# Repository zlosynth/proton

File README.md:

# Proton

Playground module for eurorack prototyping.

* This is meant to help to test ideas of new modules before they get their own
  custom hardware.
* This is not meant to be stable or simple.

# Development

See [DEVELOPMENT.md](DEVELOPMENT.md) to find some basic commands to interact
with the project.

# License

Software of Proton is distributed under the terms of the General Public
License version 3. See [LICENSE-SOFTWARE](LICENSE-SOFTWARE) for details.

Schematics and PCB layout are distributed under the terms of Creative Commons
BY-SA. See [LICENSE-HARDWARE](LICENSE-HARDWARE) for details. Parts of the
schematics are based on [Emilie Gillet's Mutable
Instruments](https://github.com/pichenettes/eurorack) and [Electrosmith's
Patch](https://www.electro-smith.com/daisy/patch) kudos to them for making them
open.

# Changelog

Read the [CHANGELOG.md](CHANGELOG.md) to learn about changes introduced in each
release.

# Versioning

See [VERSIONING.md](VERSIONING.md) to find detailed information about versioning
of the project and compatability between its software and hardware.

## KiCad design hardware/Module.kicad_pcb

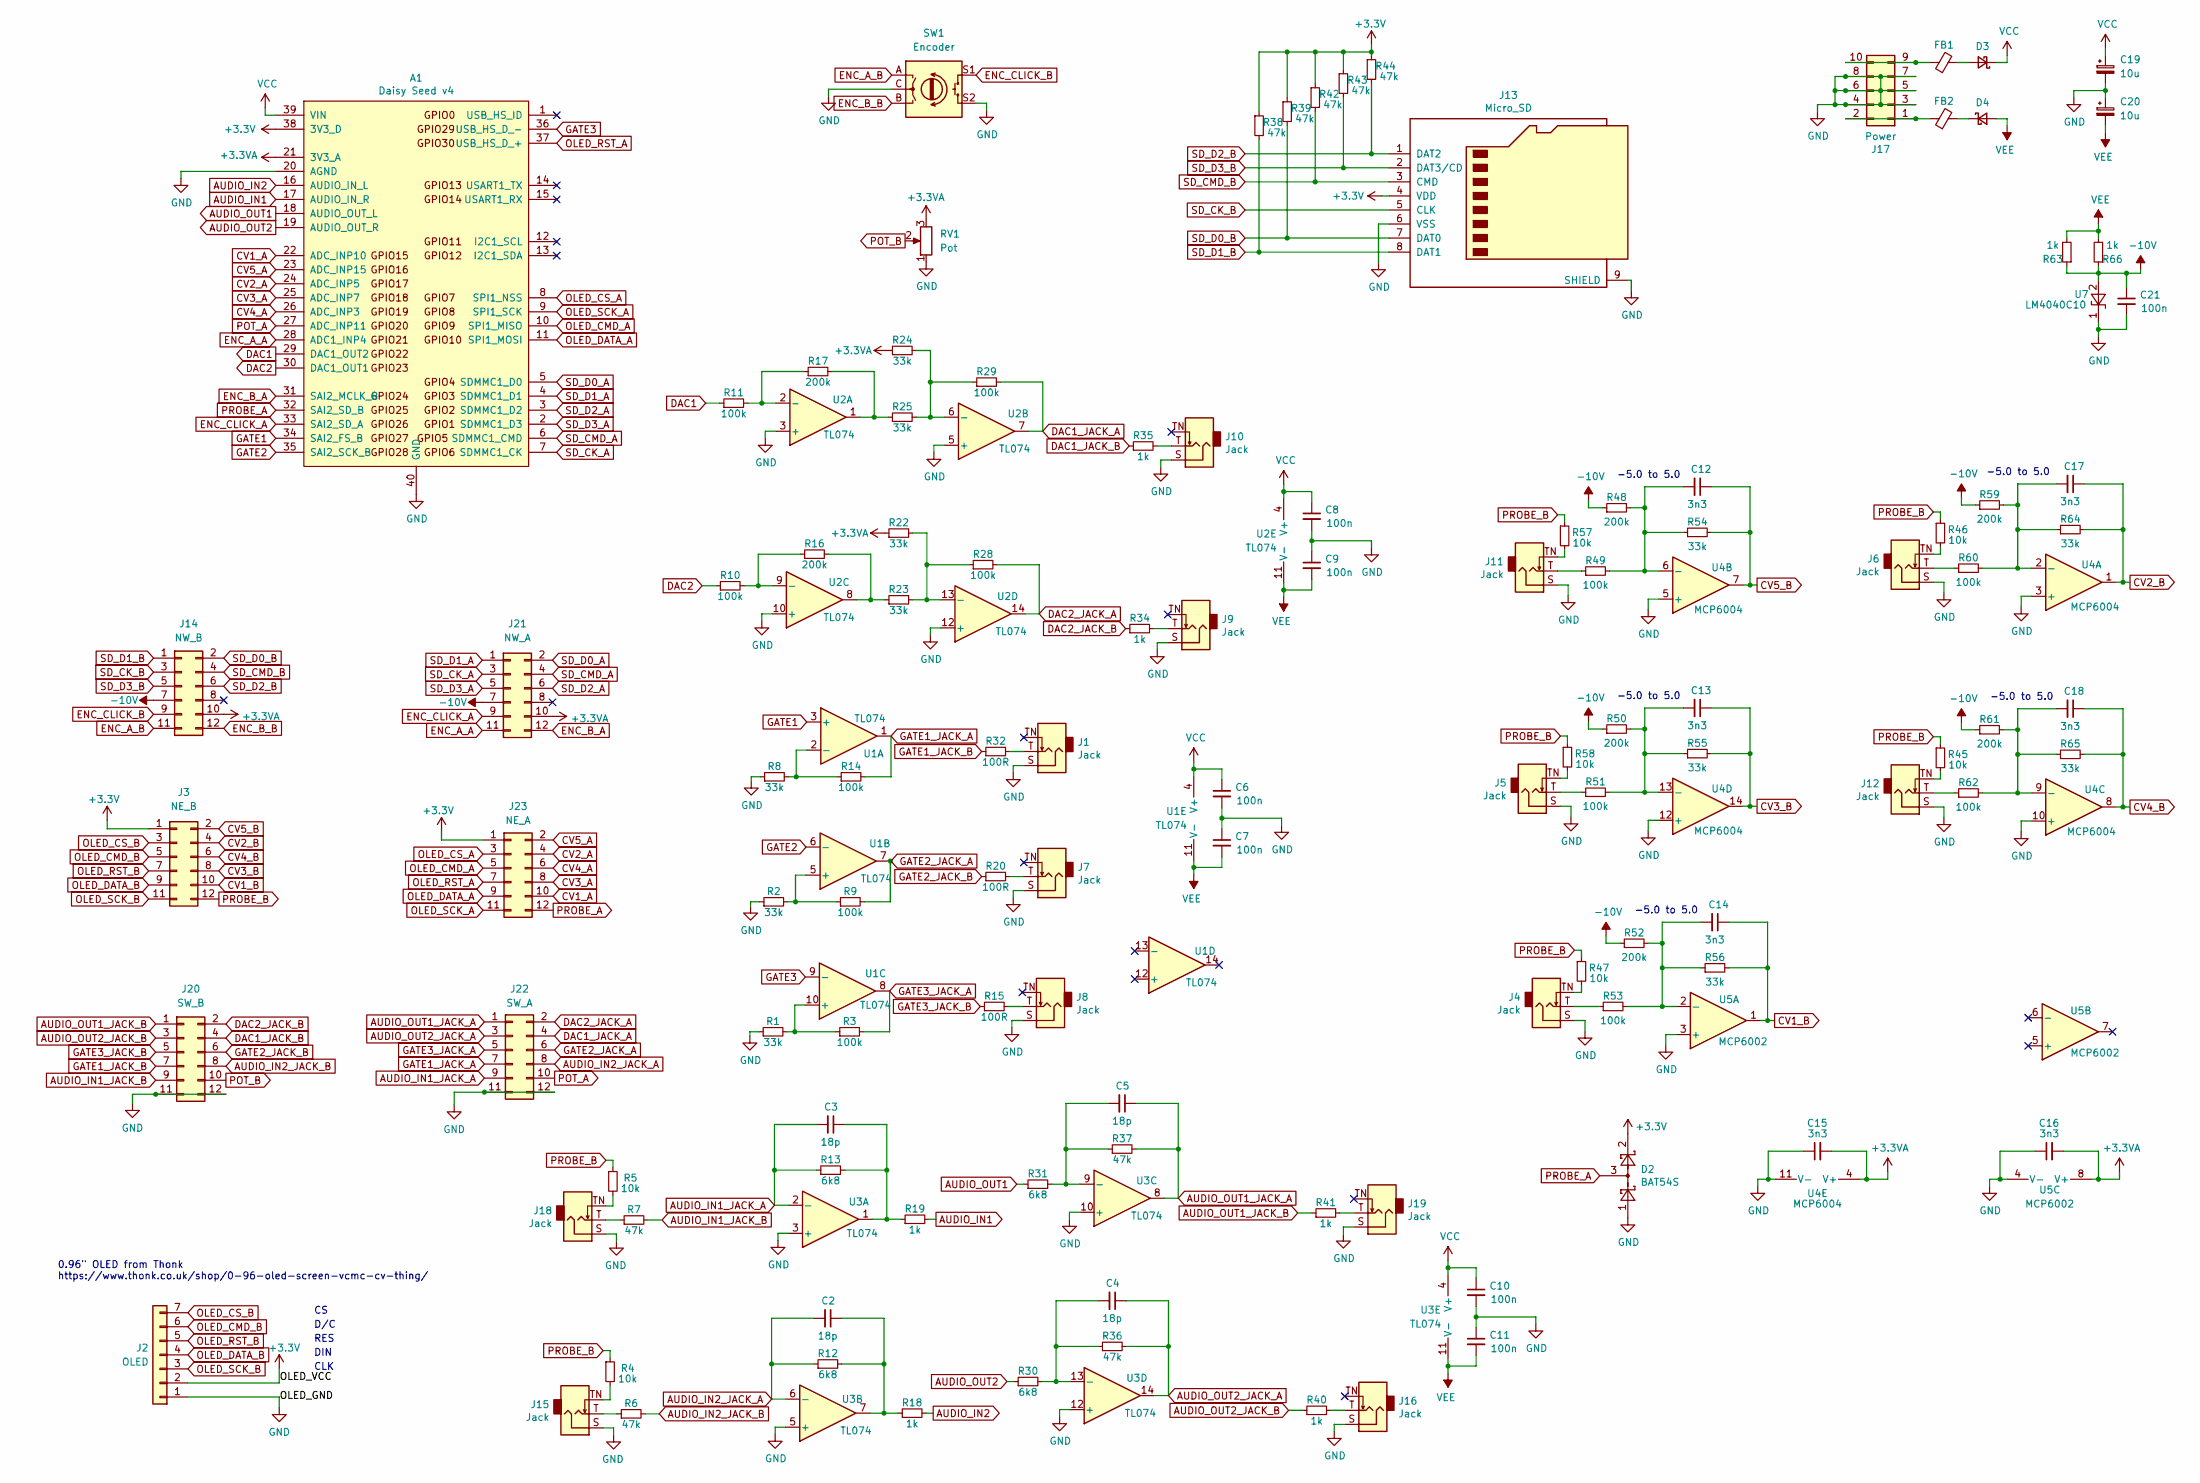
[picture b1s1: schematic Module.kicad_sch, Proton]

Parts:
A1: Daisy Seed v4; Device_Audio_Electrosmith_Daisy_Seed; Mfr Part Number M20-7822046
C2, C3, C4, C5: 18p; C_0603_1608Metric_Pad1.08x0.95mm_HandSolder; Mfr Part Number CL10C180JB81PNC; LCSC C1647
C6, C7, C8, C9, C10, C11: 100n; C_0603_1608Metric_Pad1.08x0.95mm_HandSolder; Mfr Part Number CL10F104ZO8NNNC; LCSC C14663
C12, C13, C14, C15, C16, C17, C18: 3n3; C_0603_1608Metric_Pad1.08x0.95mm_HandSolder; Mfr Part Number CL10B332KB8NNNC; LCSC C1613
C19, C20: 10u; CP_Elec_6.3x5.8
C21: 100n; C_0603_1608Metric_Pad1.08x0.95mm_HandSolder; Mfr Part Number CL31B104KBCNNNL; LCSC C24497
D2: BAT54S; SOT-23_Handsoldering; Mfr Part Number BAT54S,215
D3, D4: Schottky; D_SOD-123; Mfr Part Number STPS0540ZY; LCSC C8598
FB1, FB2: FB; L_0603_1608Metric_Pad1.05x0.95mm_HandSolder
J1, J4, J5, J6, J7, J8, J9, J10, J11, J12, J15, J16, J18, J19: Jack; Jack_3.5mm_QingPu_WQP-PJ398SM_Vertical_CircularHoles
J2: OLED; PinSocket_1x07_P2.54mm_Vertical
J3: NE_B; PinSocket_2x06_P2.54mm_Vertical
J13: Micro_SD; microsd_connector
J14: NW_B; PinSocket_2x06_P2.54mm_Vertical
J17: Power; PinHeader_2x05_P2.54mm_Vertical; Mfr Part Number 87914-1016
J20: SW_B; PinSocket_2x06_P2.54mm_Vertical
J21: NW_A; PinHeader_2x06_P2.54mm_Vertical
J22: SW_A; PinHeader_2x06_P2.54mm_Vertical
J23: NE_A; PinHeader_2x06_P2.54mm_Vertical
R1, R2, R8, R22, R23, R24, R25: 33k; R_0603_1608Metric_Pad0.98x0.95mm_HandSolder; Mfr Part Number CR0603-JW-682ELF; LCSC C23212
R3, R9, R14, R28, R29: 100k; R_0603_1608Metric_Pad0.98x0.95mm_HandSolder; Mfr Part Number CR0603-FX-4702ELF; LCSC C25819
R4, R5, R45, R46, R47, R57, R58: 10k; R_0603_1608Metric_Pad0.98x0.95mm_HandSolder; Mfr Part Number CR0603-FX-1002ELF; LCSC C25744
R6, R7: 47k; R_0603_1608Metric_Pad0.98x0.95mm_HandSolder; Mfr Part Number CR0603-JW-682ELF; LCSC C23212
R10, R11: 100k; R_0603_1608Metric_Pad0.98x0.95mm_HandSolder; Mfr Part Number CR0603-JW-682ELF; LCSC C23212
R12, R13: 6k8; R_0603_1608Metric_Pad0.98x0.95mm_HandSolder; Mfr Part Number CR0603-FX-4702ELF; LCSC C25819
R15, R20, R32: 100R; R_0603_1608Metric_Pad0.98x0.95mm_HandSolder; Mfr Part Number CR0603-FX-1001ELF; LCSC C21190
R16, R17: 200k; R_0603_1608Metric_Pad0.98x0.95mm_HandSolder; Mfr Part Number CR0603-FX-4702ELF; LCSC C25819
R18, R19, R34, R35, R40, R41, R63, R66: 1k; R_0603_1608Metric_Pad0.98x0.95mm_HandSolder; Mfr Part Number CR0603-FX-1001ELF; LCSC C21190
R30, R31: 6k8; R_0603_1608Metric_Pad0.98x0.95mm_HandSolder; Mfr Part Number CR0603-JW-682ELF; LCSC C23212
R36, R37: 47k; R_0603_1608Metric_Pad0.98x0.95mm_HandSolder; Mfr Part Number CR0603-FX-4702ELF; LCSC C25819
R38, R39, R42, R43, R44: 47k; R_0603_1608Metric_Pad0.98x0.95mm_HandSolder; Mfr Part Number CR0603-FX-1002ELF; LCSC C25744
R48: 200k; R_0603_1608Metric_Pad0.98x0.95mm_HandSolder; Mfr Part Number CR0603-FX-1803ELF; LCSC C25808
R49, R51, R53, R60, R62: 100k; R_0603_1608Metric_Pad0.98x0.95mm_HandSolder; Mfr Part Number CR0603-JW-104ELF; LCSC C25803
R50: 200k; R_0603_1608Metric_Pad0.98x0.95mm_HandSolder; Mfr Part Number CR0603-FX-1203ELF; LCSC C22827
R52, R61: 200k; R_0603_1608Metric_Pad0.98x0.95mm_HandSolder; Mfr Part Number CR0603-FX-1203ELF; LCSC C25808
R54: 33k; R_0603_1608Metric_Pad0.98x0.95mm_HandSolder; Mfr Part Number CR0603-FX-4702ELF; LCSC C4184
R55: 33k; R_0603_1608Metric_Pad0.98x0.95mm_HandSolder; Mfr Part Number CR0603-FX-2002ELF; LCSC C25819
R56, R65: 33k; R_0603_1608Metric_Pad0.98x0.95mm_HandSolder; Mfr Part Number CR0603-FX-2002ELF; LCSC C4184
R59: 200k; R_0603_1608Metric_Pad0.98x0.95mm_HandSolder; Mfr Part Number CR0603-FX-1803ELF; LCSC C22827
R64: 33k; R_0603_1608Metric_Pad0.98x0.95mm_HandSolder; Mfr Part Number CR0603-FX-4702ELF; LCSC C25819
RV1: Pot; Potentiometer_Alpha_RD901F-40-00D_Single_Vertical
SW1: Encoder; RotaryEncoder_Alps_EC11E-Switch_Vertical_H20mm
U1, U2, U3: TL074; SOIC-14_3.9x8.7mm_P1.27mm
U4: MCP6004; SOIC-14_3.9x8.7mm_P1.27mm
U5: MCP6002; SOIC-8_3.9x4.9mm_P1.27mm; Mfr Part Number MCP6002-I/SN; LCSC C7377
U7: LM4040C10; SOT-23_Handsoldering; Mfr Part Number LM4040C10IDBZR; LCSC C201738

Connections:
+3.3VA: A1.21 (3V3_A), C15.2, C16.2, J14.10, J21.10, R22.1, R24.1, RV1.3, U4.4 (V+), U5.8 (V+)
+3V3: A1.38 (3V3_D), D2.2, J2.2, J3.1, J13.4 (VDD), J23.1, R38.1, R39.1, R42.1, R43.1, R44.1
-10V: C21.1, J14.7, J21.7, R48.1, R50.1, R52.1, R59.1, R61.1, R63.1, R66.1, U7.2 (A)
AUDIO_IN1: A1.17 (AUDIO_IN_R), R19.2
AUDIO_IN1_JACK_A: C3.2, J22.9, R13.1, U3.2 (-)
AUDIO_IN1_JACK_B: J20.9, R7.2
AUDIO_IN2: A1.16 (AUDIO_IN_L), R18.2
AUDIO_IN2_JACK_A: C2.2, J22.8, R12.1, U3.6 (-)
AUDIO_IN2_JACK_B: J20.8, R6.2
AUDIO_OUT1: A1.18 (AUDIO_OUT_L), R31.1
AUDIO_OUT1_JACK_A: C5.1, J22.1, R37.2, U3.8
AUDIO_OUT1_JACK_B: J20.1, R41.1
AUDIO_OUT2: A1.19 (AUDIO_OUT_R), R30.1
AUDIO_OUT2_JACK_A: C4.1, J22.3, R36.2, U3.14
AUDIO_OUT2_JACK_B: J20.3, R40.1
CV1_A: A1.22 (ADC_INP10), J23.10
CV1_B: C14.1, J3.10, R56.2, U5.1
CV2_A: A1.24 (ADC_INP5), J23.4
CV2_B: C17.1, J3.4, R64.2, U4.1
CV3_A: A1.25 (ADC_INP7), J23.8
CV3_B: C13.1, J3.8, R55.2, U4.14
CV4_A: A1.26 (ADC_INP3), J23.6
CV4_B: C18.1, J3.6, R65.2, U4.8
CV5_A: A1.23 (ADC_INP15), J23.2
CV5_B: C12.1, J3.2, R54.2, U4.7
DAC1: A1.29 (DAC1_OUT2), R11.1
DAC1_JACK_A: J22.4, R29.2, U2.7
DAC1_JACK_B: J20.4, R35.1
DAC2: A1.30 (DAC1_OUT1), R10.1
DAC2_JACK_A: J22.2, R28.2, U2.14
DAC2_JACK_B: J20.2, R34.1
ENC_A_A: A1.28 (ADC1_INP4), J21.11
ENC_A_B: J14.11, SW1.A
ENC_B_A: A1.31 (SAI2_MCLK_B), J21.12
ENC_B_B: J14.12, SW1.B
ENC_CLICK_A: A1.33 (SAI2_SD_A), J21.9
ENC_CLICK_B: J14.9, SW1.S1
GATE1: A1.34 (SAI2_FS_B), U1.3 (+)
GATE1_JACK_A: J22.7, R14.2, U1.1
GATE1_JACK_B: J20.7, R32.1
GATE2: A1.35 (SAI2_SCK_B), U1.6 (-)
GATE2_JACK_A: J22.6, R9.2, U1.7
GATE2_JACK_B: J20.6, R20.1
GATE3: A1.36 (USB_HS_D_-), U1.9 (-)
GATE3_JACK_A: J22.5, R3.2, U1.8
GATE3_JACK_B: J20.5, R15.1
GND: A1.20 (AGND), A1.40 (GND), C6.2, C7.1, C8.2, C9.1, C10.2, C11.1, C15.1, C16.1, C19.2, C20.1, C21.2, D2.1, J1.S, J2.1, J4.S, J5.S, J6.S, J7.S, J8.S, J9.S, J10.S, J11.S, J12.S, J13.6 (VSS), J13.9 (SHIELD), J15.S, J16.S, J17.3, J17.4, J17.5, J17.6, J17.7, J17.8, J18.S, J19.S, J20.11, J20.12, J22.11, J22.12, R1.1, R2.1, R8.1, RV1.1, SW1.C, SW1.S2, U2.3 (+), U2.5 (+), U2.10 (+), U2.12 (+), U3.3 (+), U3.5 (+), U3.10 (+), U3.12 (+), U4.3 (+), U4.5 (+), U4.10 (+), U4.11 (V-), U4.12 (+), U5.3 (+), U5.4 (V-), U7.1 (K)
unnamed: C2.1, R12.2, R18.1, U3.7
unnamed: C3.1, R13.2, R19.1, U3.1
unnamed: C4.2, R30.2, R36.1, U3.13 (-)
unnamed: C5.2, R31.2, R37.1, U3.9 (-)
unnamed: C12.2, R48.2, R49.2, R54.1, U4.6 (-)
unnamed: C13.2, R50.2, R51.2, R55.1, U4.13 (-)
unnamed: C14.2, R52.2, R53.2, R56.1, U5.2 (-)
unnamed: C17.2, R59.2, R60.2, R64.1, U4.2 (-)
unnamed: C18.2, R61.2, R62.2, R65.1, U4.9 (-)
unnamed: D3.2 (A), FB1.2
unnamed: D4.1 (K), FB2.2
unnamed: FB1.1, J17.9, J17.10
unnamed: FB2.1, J17.1, J17.2
unnamed: J1.T, R32.2
unnamed: J4.T, R53.1
unnamed: J4.TN, R47.2
unnamed: J5.T, R51.1
unnamed: J5.TN, R58.2
unnamed: J6.T, R60.1
unnamed: J6.TN, R46.2
unnamed: J7.T, R20.2
unnamed: J8.T, R15.2
unnamed: J9.T, R34.2
unnamed: J10.T, R35.2
unnamed: J11.T, R49.1
unnamed: J11.TN, R57.2
unnamed: J12.T, R62.1
unnamed: J12.TN, R45.2
unnamed: J15.T, R6.1
unnamed: J15.TN, R4.2
unnamed: J16.T, R40.2
unnamed: J18.T, R7.1
unnamed: J18.TN, R5.2
unnamed: J19.T, R41.2
unnamed: R1.2, R3.1, U1.10 (+)
unnamed: R2.2, R9.1, U1.5 (+)
unnamed: R10.2, R16.1, U2.9 (-)
unnamed: R11.2, R17.1, U2.2 (-)
unnamed: R8.2, R14.1, U1.2 (-)
unnamed: R16.2, R23.1, U2.8
unnamed: R17.2, R25.1, U2.1
unnamed: R22.2, R23.2, R28.1, U2.13 (-)
unnamed: R24.2, R25.2, R29.1, U2.6 (-)
OLED_CMD_A: A1.10 (SPI1_MISO), J23.5
OLED_CMD_B: J2.6, J3.5
OLED_CS_A: A1.8 (SPI1_NSS), J23.3
OLED_CS_B: J2.7, J3.3
OLED_DATA_A: A1.11 (SPI1_MOSI), J23.9
OLED_DATA_B: J2.4, J3.9
OLED_RST_A: A1.37 (USB_HS_D_+), J23.7
OLED_RST_B: J2.5, J3.7
OLED_SCK_A: A1.9 (SPI1_SCK), J23.11
OLED_SCK_B: J2.3, J3.11
POT_A: A1.27 (ADC_INP11), J22.10
POT_B: J20.10, RV1.2
PROBE_A: A1.32 (SAI2_SD_B), D2.3, J23.12
PROBE_B: J3.12, R4.1, R5.1, R45.1, R46.1, R47.1, R57.1, R58.1
SD_CK_A: A1.7 (SDMMC1_CK), J21.3
SD_CK_B: J13.5 (CLK), J14.3
SD_CMD_A: A1.6 (SDMMC1_CMD), J21.4
SD_CMD_B: J13.3 (CMD), J14.4, R42.2
SD_D0_A: A1.5 (SDMMC1_D0), J21.2
SD_D0_B: J13.7 (DAT0), J14.2, R39.2
SD_D1_A: A1.4 (SDMMC1_D1), J21.1
SD_D1_B: J13.8 (DAT1), J14.1, R38.2
SD_D2_A: A1.3 (SDMMC1_D2), J21.6
SD_D2_B: J13.1 (DAT2), J14.6, R44.2
SD_D3_A: A1.2 (SDMMC1_D3), J21.5
SD_D3_B: J13.2 (DAT3/CD), J14.5, R43.2
VCC: A1.39 (VIN), C6.1, C8.1, C10.1, C19.1, D3.1 (K), U1.4 (V+), U2.4 (V+), U3.4 (V+)
VEE: C7.2, C9.2, C11.2, C20.2, D4.2 (A), R63.2, R66.2, U1.11 (V-), U2.11 (V-), U3.11 (V-)

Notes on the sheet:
-5.0 to 5.0
0.96" OLED from Thonk https://www.thonk.co.uk/shop/0-96-oled-screen-vcmc-cv-thing/
CLK
RES
DIN
D/C

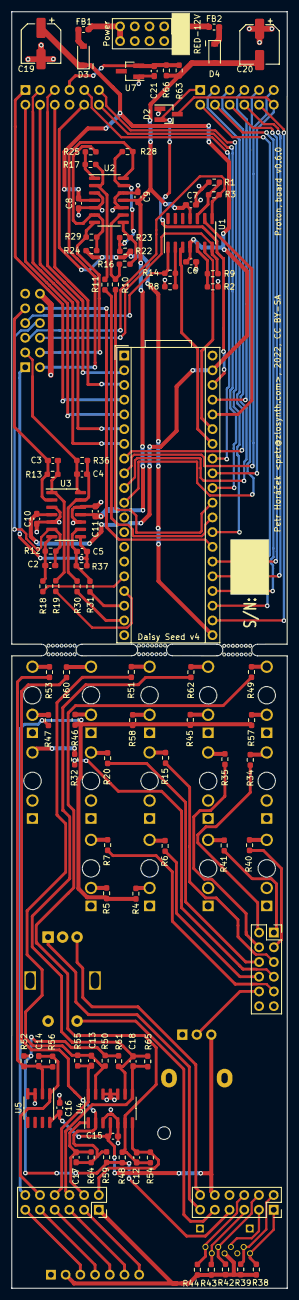
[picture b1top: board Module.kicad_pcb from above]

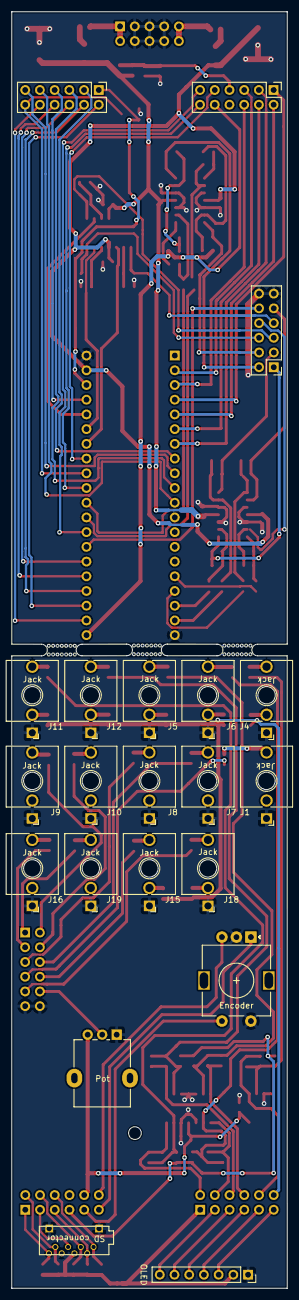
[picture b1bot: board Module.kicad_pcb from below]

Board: 2 copper layers, 47.6 x 220.4 mm, 122 parts (21 on the bottom side), 118 nets.

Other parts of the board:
mouse-bite-2mm-slot, mouse-bite-2mm-slot#2, mouse-bite-2mm-slot#3: VAL**; mouse-bite-2mm-slot

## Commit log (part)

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2022-02-27 Initialize the project with READMEs and licensing
2022-02-27 Add sketch of the front panel
2022-02-27 Initialize the hardware with Achordion
2022-03-02 Add SD card footprint
2022-03-02 Update changelog with added schematics
2022-03-03 Fix spacing of components on the sketch
    It should now match the spacing on Achordion.
2022-03-06 Design the PCB
2022-03-06 Remove a leftover dot on PCB
2022-03-06 Remove misleading label
2022-04-29 Update to KiCad 6
2022-04-29 Introduce a makefile
2022-04-29 Introduce GitHub Actions CI
2022-04-29 Add LICENSE for software
2022-04-29 Introduce basic sawtooth oscillator
2022-04-29 Add simple oscillator module binding
2022-04-30 Implement basic hardcoded patch
2022-04-30 Remove unnecessary package for core
2022-04-30 Implement puredata binding for testing
2022-04-30 Update the changelog
2022-04-30 Introduce script for release updates
2022-04-30 Move engine under core/
2022-04-30 Introduce abstraction for signal buffer
2022-04-30 Abstract audio output data cells
2022-04-30 Introduce an instrument wrapper
    This will later get extended with UI and high level logic.
2022-04-30 Implement basic stub for display
2022-05-01 Implement page selection in UI
2022-05-01 Draw scroll bar for module pages
2022-05-01 Add helped function for text drawing
2022-05-01 Display index of each module
2022-05-01 Deduce module page from selected module
2022-05-01 Highlight selected consumer
2022-05-01 Display multiple pages of attributes
2022-05-01 Display whether attribute is connected
2022-05-01 Display attribute value
2022-05-01 Move store ownership to instrument
2022-05-01 Rename store to state
    Store will be used for persistence. State is just for runtime.
2022-05-01 Merge engine into instrument
    For easier high level work until it gets its own abstraction again.
2022-05-01 Store all graph indices in state
2022-05-01 Allow cloning and comparing of state
2022-05-01 Make state generic for any graph
2022-05-01 Integrate encoder scroll action into puredata
2022-05-01 external: Keep insturment in global
    When kept under class, it causes seg faults. Probably can't fit in
    there.
2022-05-01 display: Introduce cursor abstraction
2022-05-01 display: Adjust spacing on patch list
2022-05-01 display: Highlight selected patch
2022-05-01 model: Implement alpha scroll up
2022-05-01 model: Add helped function to populate state
2022-05-02 display: Highlight the whole line
2022-05-02 display: Remove placeholder values field
2022-05-02 display: Connected attr icon based on direction
2022-05-02 Document display changes in changelog
2022-05-02 Release version 0.2.0
2022-05-03 modules: Introduce trait for module template
2022-05-03 display: Show arrow between patch ends
2022-05-03 model: Implement disconnecting of patch source
2022-05-04 instrument: Implement disconnecting of patches
2022-05-04 display: Split draw_patch function
    This will make it easier to draw other modes of edit.
2022-05-04 model: Implement helpers to build state
2022-05-04 model: Make patch destination required
2022-05-06 model: Make reduce routing cleaner
2022-05-06 display: Show multiple pages of patches
2022-05-06 display: Show scrollbar in patches view
2022-05-06 display: Show scroll bar for source selection
2022-05-06 display: Remove redundant function
2022-05-06 model: Select source even on hold
2022-05-06 model: Scroll patches witch both alpha and beta
2022-05-06 model: Remove resolved TODO
2022-05-07 model, display: Add module classes
2022-05-07 model: Implement navigation in module add view
2022-05-07 model: Pass graph to reducer
    It will have a performance hit as graph needs to be locked and cannot be
    used by DSP. Let's see if it matters.
2022-05-07 Introduce support for module instantiation
2022-05-07 Fix formatting
2022-05-07 Switch to module adding when both clicked
2022-05-07 Introduce support for module removal
2022-05-07 Use builder pattern to instantiate Modules
2022-05-08 Assign a unique index to each new module
2022-05-08 Fix an issue where repatching was not allowed
2022-05-08 Use builders to create persistent modules
2022-05-08 Release version 0.3.0
2022-05-12 Extend RTIC stub to run blinky
2022-05-12 Implement basic display example
2022-05-15 Add a display integration test
2022-05-19 Remove eurorack/README
    It is documented under DEVELOPMENT.
2022-05-21 Replace plot_pcb with plot_assembly
    Gerbers are now rendered with JLC extensions.
2022-05-21 Make value labels on assembly plan visible
2022-05-21 Integrate display in firmware
2022-05-22 Implement abstraction for rotary encoder
2022-05-22 Split updating and reading in rotary abstraction
2022-05-22 Implement debouncer abstraction
2022-05-22 Rename debouncer buffer to debounce
2022-05-22 Implement button abstraction
2022-05-22 Implement abstraction of an encoder
2022-05-22 Control instrument via encoders
    This shows that the instrument is not viable here. It does not implement
    Send and sharing display, control input queue and audio in one entity
    would not fly.
2022-05-22 Use already defined display type
2022-05-22 Move user input handling to separate library
2022-05-22 Use encoder button in display test
2022-05-24 Implement new UI showing attributes
    This one is made simpler and the data model should be ready for
    multi-threaded model.
2022-05-24 Implement dedicated View struct for display
    This will split heavy Status and Copy-able View.
2022-05-25 Use channel between input and state in firmware
2022-05-26 Simplify rotary handling and increase priority
    This way it should not compete with display time.
2022-05-26 Use left encoder to move through attributes
2022-05-27 Recover from corrupted encoder state
2022-05-27 Use builder patter to construct state
2022-05-27 Implement setting of f32 values through encoder
2022-05-27 Always reset display before drawing
    This makes sure fragment don't stay on the screen between changes.
2022-05-27 Clean up input initialization
2022-05-27 Remove unnecessary logs from firmware
2022-05-27 Switch puredata to use the new ui
2022-05-27 Introduce state variable filter module
2022-05-27 Fix embedded tests and add check for them
2022-05-28 Prototype a karplus strong synth box
2022-05-28 Install SDL library on GitHub actions
2022-05-28 Fix release script to find all Cargo.toml
2022-05-28 Introduce a stub of karplus strong music box
2022-05-28 Release version 0.4.0
2022-05-28 Return Reaction from reducer
2022-05-28 Accept reactions in karplus strong instrument
2022-05-28 Utilize the new instrument in firmware
2022-05-28 Wire up firmware audio
2022-05-28 Add AD envelope primitive
2022-05-28 Update changelog with recent changes
2022-05-28 Shorten the name of karplus strong
2022-05-28 Implement frequency+feedback control in karplus
2022-05-29 Explain how to check size of firmware
2022-05-29 Allow custom settings for f32 attribute range
2022-05-29 Allow configuration of custom f32 formatting
2022-06-03 Introduce a turing-like sequencer
2022-06-04 Implement a simple turing machine-like sequencer
    With this patch, the sequencer generates random rhythm, and iterates on
    it, slowly changing it.
2022-06-05 Allow control of rate and density
2022-06-05 Implement selectable note length
2022-06-05 Allow control of beats in bar
2022-06-05 Quantize to major pentatonic
2022-06-05 Fix initial frequency setting
2022-06-13 Introduce a tape emulator stub
2022-06-13 Add the first control attribute for tape
2022-06-14 Implement post gain command
2022-06-14 Move tape instrument into its own package
2022-06-14 Fix puredata wrapper logic for inlets
2022-06-19 Remove unnecessary trait requirement
2022-06-19 Be specific about the used frame type
2022-06-25 Expose tape instrument through firmware
2022-06-26 Create a script for hysteresis design
2022-06-26 Increase sample rate to capture oversampling
2022-06-28 Implement realtime hysteresis processing in tape
2022-06-28 Implement control of tweak parameters
2022-07-03 Optimize upsampling filter
    No need to multiply coefficients by zeroed values of the signal.
2022-07-03 Optimized decimating filter
2022-07-03 Move oversampling model under primitives
2022-07-03 Add kudos to oversampling module
2022-07-03 Implement downsampling over Signal trait
2022-07-04 Persist oversampling state between buffers
2022-07-04 Use the actual sample rate in pd external
2022-07-04 Fix sinc filter coefficients
2022-07-04 Make tape instrument chain more compact
2022-07-04 Fix clippy in spectral analysis module
2022-07-04 Silence invalid clippy warnings
2022-07-04 Adjust "close-to-zero" detection in langevin
2022-07-05 Clip input amplitude to stay stable
2022-07-05 Add adc to pure data external
2022-07-05 Limit the output value of hysteresis
2022-07-05 Select instruments through features
2022-07-10 Improve formating of UI docs
2022-07-10 Process all CV inputs in firmware
2022-07-10 Wire control input from pure data to instruments
2022-07-10 Control some of the karplus strong args via cv
2022-07-10 Control tape through CV
2022-07-10 Introduce benchmark for tape instrument
2022-07-10 Create a crude graph of amplitude response
    This will later serve to makeup for amplitude based on hysteresis
    parameters. The range has to be however limited first.
2022-07-11 Widen the range of simulated width attributes
2022-07-11 Implement debug for Tape instrument
    This allows dump of the current tape state.
2022-07-21 Create a model for stable hysteresis amplitude
2022-07-26 Script fitting curve for stable amplitude
2022-08-07 Remove MIDI from the sketch
2022-08-09 Place THT on two-layer PCB
2022-08-10 Wire up all connections
2022-08-10 Add S/N silkscreen
2022-08-10 Add mouse bites to footprint library
2022-08-10 Don't keep gerbers under git
2022-08-10 Mark pins without connections
2022-08-10 Fix all DRC checks
2022-08-11 Assign parts from JLCPCB
2022-08-11 Adjust some parts
2022-08-11 Update changelog with recent HW changes
2022-08-11 Release version 0.6.0
2022-08-11 Replace one of the encoders with a pot
    For better eurorack feel. And one encoder is well enough.
2022-08-26 Register pot in system and test it
2022-08-26 Use defmt_init in display test
2022-08-27 Pass instrument type to embedded tests
2022-08-27 Change display while testing it
2022-08-27 Adjust rotary peripheral to the new encoder
    The new shorter encoder takes only 2 steps for transition.
2022-08-27 Adjust CV input mapping to the new layout
2022-08-27 Fix embedded test button waiting
2022-08-27 Test gate outputs and document its bugs
2022-08-27 Add changelog entries for new hardware
2022-08-27 Use a single delay for initialization of system
2022-08-27 Implement CV output
2022-08-27 Introduce pot to input processor snapshot
2022-08-27 Apply CV input on eurorack instrument
2022-08-27 Introduce stub of Kaseta binding
2022-08-30 Remove global allocator and archive karplus strong
2022-08-30 Remove karplus strong and tape
2022-08-30 Switch to stable rust and remove primitives
2022-08-30 Use released daisy
2022-08-30 Use LTO
2022-08-30 Slim down the firmware
    Removing formatting of f32 brings firmware size from 87608 B to 42320 B.
2022-08-31 Remove unused random trait
2022-08-31 Define a trait for instruments
2022-08-31 Implement static processing through kaseta
    Unusuable due to processing requirements of hysteresis.
2022-08-31 Update dependencies
2022-09-12 Fix docstring for cache
2022-09-12 Don't panic on full input queue
2022-09-12 Bind CV inputs to kaseta
2022-10-15 Bind kaseta delay
2022-10-18 Bind kaseta rewind and delay range
2022-10-26 Pin to an official daisy release
2022-11-10 Fetch kaseta from its oficial release
2022-11-10 Align style of illustration with Achordion
2022-11-10 Align jack style on illustration with Achordion
2023-09-17 Replace kaseta with a stub of a new module
2023-09-17 track: Implement basic audio passthrough
2023-09-17 Fix make target
2023-09-27 Add sdmmc system abstraction
2023-09-27 Pass SD card interface to instruments
2023-09-27 Initialize SD card before passing it
2023-09-28 Introduce helper function creating sample
2023-09-28 Implement pitch shifting
2023-10-01 Design dynamic buffer
2023-10-01 Draft of track recorder buffer

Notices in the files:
hardware/Module.kicad_pcb:
cc-by-sa
Petr Horáček , 2022, CC BY-SA
